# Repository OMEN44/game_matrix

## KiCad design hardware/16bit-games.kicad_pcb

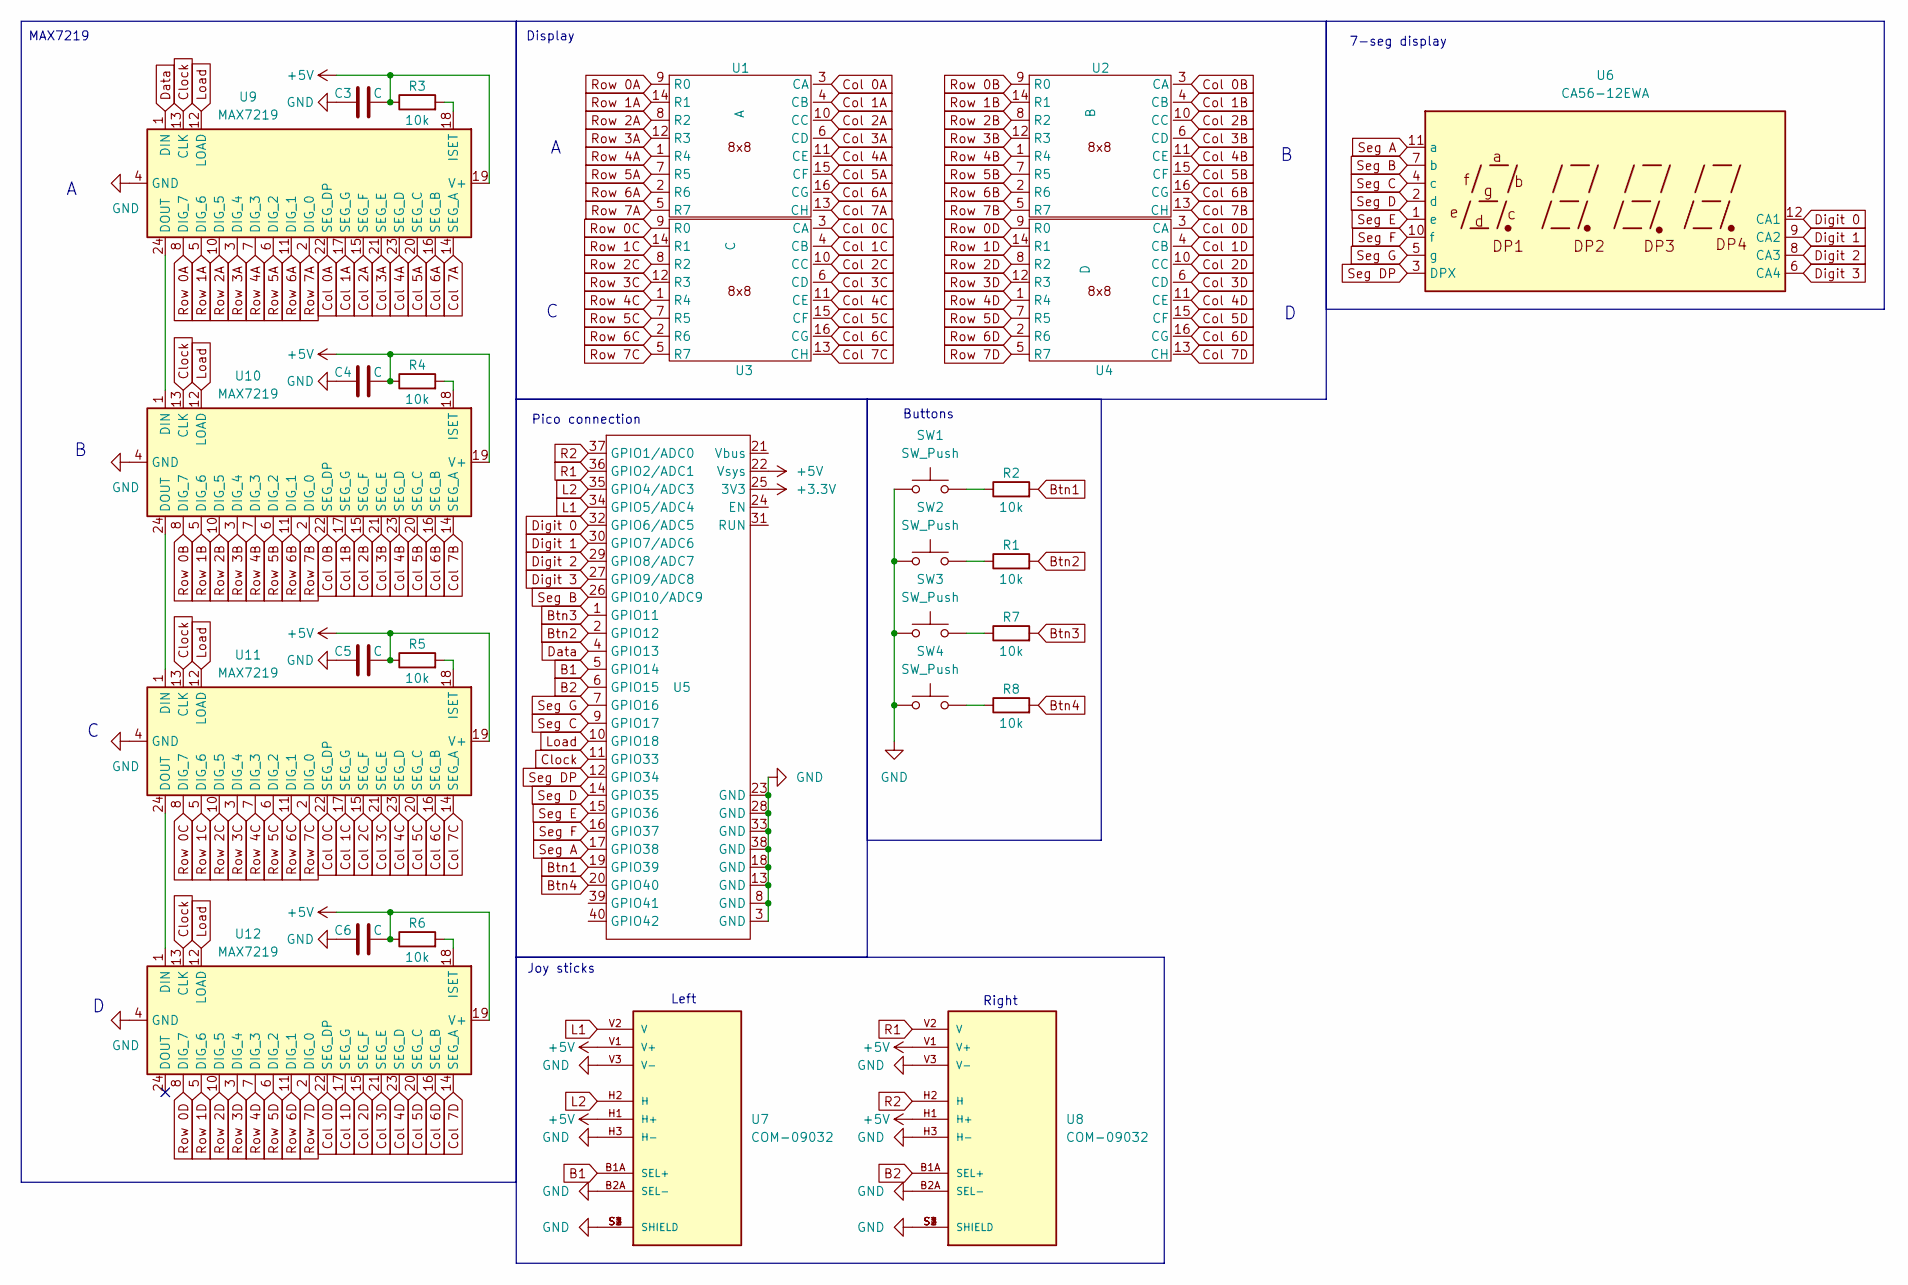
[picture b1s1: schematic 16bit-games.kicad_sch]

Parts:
C3, C4, C5, C6: C; C_Radial_D6.3mm_H5.0mm_P2.50mm
R1, R2, R3, R4, R5, R6, R7, R8: 10k; R_Axial_DIN0204_L3.6mm_D1.6mm_P7.62mm_Horizontal
SW1, SW2, SW3, SW4: SW_Push; SW_PUSH_6mm_H4.3mm
U1: A; 8x8
U2: B; 8x8
U3: C; 8x8
U4: D; 8x8
U5: ESP32-Pico
U6: CA56-12EWA; 4x7-seg Display
U7, U8: COM-09032; XDCR_COM-09032; PARTREV N/A
U9, U10, U11, U12: MAX7219; DIP-24_W7.62mm

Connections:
+3.3V: U5.25 (3V3)
+5V: C3.2, C4.2, C5.2, C6.2, R3.1, R4.1, R5.1, R6.1, U5.22 (Vsys), U7.H1 (H+), U7.V1 (V+), U8.H1 (H+), U8.V1 (V+), U9.19 (V+), U10.19 (V+), U11.19 (V+), U12.19 (V+)
B1: U5.5 (GPIO14), U7.B1A (SEL+)
B2: U5.6 (GPIO15), U8.B1A (SEL+)
Btn1: R2.2, U5.19 (GPIO39)
Btn2: R1.2, U5.2 (GPIO12)
Btn3: R7.2, U5.1 (GPIO11)
Btn4: R8.2, U5.20 (GPIO40)
Clock: U5.11 (GPIO33), U9.13 (CLK), U10.13 (CLK), U11.13 (CLK), U12.13 (CLK)
Col 0A: U1.3 (CA), U9.22 (SEG_DP)
Col 0B: U2.3 (CA), U10.22 (SEG_DP)
Col 0C: U3.3 (CA), U11.22 (SEG_DP)
Col 0D: U4.3 (CA), U12.22 (SEG_DP)
Col 1A: U1.4 (CB), U9.17 (SEG_G)
Col 1B: U2.4 (CB), U10.17 (SEG_G)
Col 1C: U3.4 (CB), U11.17 (SEG_G)
Col 1D: U4.4 (CB), U12.17 (SEG_G)
Col 2A: U1.10 (CC), U9.15 (SEG_F)
Col 2B: U2.10 (CC), U10.15 (SEG_F)
Col 2C: U3.10 (CC), U11.15 (SEG_F)
Col 2D: U4.10 (CC), U12.15 (SEG_F)
Col 3A: U1.6 (CD), U9.21 (SEG_E)
Col 3B: U2.6 (CD), U10.21 (SEG_E)
Col 3C: U3.6 (CD), U11.21 (SEG_E)
Col 3D: U4.6 (CD), U12.21 (SEG_E)
Col 4A: U1.11 (CE), U9.23 (SEG_D)
Col 4B: U2.11 (CE), U10.23 (SEG_D)
Col 4C: U3.11 (CE), U11.23 (SEG_D)
Col 4D: U4.11 (CE), U12.23 (SEG_D)
Col 5A: U1.15 (CF), U9.20 (SEG_C)
Col 5B: U2.15 (CF), U10.20 (SEG_C)
Col 5C: U3.15 (CF), U11.20 (SEG_C)
Col 5D: U4.15 (CF), U12.20 (SEG_C)
Col 6A: U1.16 (CG), U9.16 (SEG_B)
Col 6B: U2.16 (CG), U10.16 (SEG_B)
Col 6C: U3.16 (CG), U11.16 (SEG_B)
Col 6D: U4.16 (CG), U12.16 (SEG_B)
Col 7A: U1.13 (CH), U9.14 (SEG_A)
Col 7B: U2.13 (CH), U10.14 (SEG_A)
Col 7C: U3.13 (CH), U11.14 (SEG_A)
Col 7D: U4.13 (CH), U12.14 (SEG_A)
Data: U5.4 (GPIO13), U9.1 (DIN)
Digit 0: U5.32 (GPIO6/ADC5), U6.12 (CA1)
Digit 1: U5.30 (GPIO7/ADC6), U6.9 (CA2)
Digit 2: U5.29 (GPIO8/ADC7), U6.8 (CA3)
Digit 3: U5.27 (GPIO9/ADC8), U6.6 (CA4)
GND: C3.1, C4.1, C5.1, C6.1, SW1.1, SW2.1, SW3.1, SW4.1, U5.3 (GND), U5.8 (GND), U5.13 (GND), U5.18 (GND), U5.23 (GND), U5.28 (GND), U5.33 (GND), U5.38 (GND), U7.B2A (SEL-), U7.H3 (H-), U7.S1 (SHIELD), U7.S2 (SHIELD), U7.S3 (SHIELD), U7.S4 (SHIELD), U7.V3 (V-), U8.B2A (SEL-), U8.H3 (H-), U8.S1 (SHIELD), U8.S2 (SHIELD), U8.S3 (SHIELD), U8.S4 (SHIELD), U8.V3 (V-), U9.4 (GND), U9.9 (GND), U10.4 (GND), U10.9 (GND), U11.4 (GND), U11.9 (GND), U12.4 (GND), U12.9 (GND)
L1: U5.34 (GPIO5/ADC4), U7.V2 (V)
L2: U5.35 (GPIO4/ADC3), U7.H2 (H)
Load: U5.10 (GPIO18), U9.12 (LOAD), U10.12 (LOAD), U11.12 (LOAD), U12.12 (LOAD)
unnamed: R1.1, SW2.2
unnamed: R2.1, SW1.2
unnamed: R7.1, SW3.2
unnamed: R8.1, SW4.2
unnamed: R3.2, U9.18 (ISET)
unnamed: U9.24 (DOUT), U10.1 (DIN)
unnamed: U10.24 (DOUT), U11.1 (DIN)
unnamed: R4.2, U10.18 (ISET)
unnamed: U11.24 (DOUT), U12.1 (DIN)
unnamed: R5.2, U11.18 (ISET)
unnamed: R6.2, U12.18 (ISET)
R1: U5.36 (GPIO2/ADC1), U8.V2 (V)
R2: U5.37 (GPIO1/ADC0), U8.H2 (H)
Row 0A: U1.9 (R0), U9.8 (DIG_7)
Row 0B: U2.9 (R0), U10.8 (DIG_7)
Row 0C: U3.9 (R0), U11.8 (DIG_7)
Row 0D: U4.9 (R0), U12.8 (DIG_7)
Row 1A: U1.14 (R1), U9.5 (DIG_6)
Row 1B: U2.14 (R1), U10.5 (DIG_6)
Row 1C: U3.14 (R1), U11.5 (DIG_6)
Row 1D: U4.14 (R1), U12.5 (DIG_6)
Row 2A: U1.8 (R2), U9.10 (DIG_5)
Row 2B: U2.8 (R2), U10.10 (DIG_5)
Row 2C: U3.8 (R2), U11.10 (DIG_5)
Row 2D: U4.8 (R2), U12.10 (DIG_5)
Row 3A: U1.12 (R3), U9.3 (DIG_4)
Row 3B: U2.12 (R3), U10.3 (DIG_4)
Row 3C: U3.12 (R3), U11.3 (DIG_4)
Row 3D: U4.12 (R3), U12.3 (DIG_4)
Row 4A: U1.1 (R4), U9.7 (DIG_3)
Row 4B: U2.1 (R4), U10.7 (DIG_3)
Row 4C: U3.1 (R4), U11.7 (DIG_3)
Row 4D: U4.1 (R4), U12.7 (DIG_3)
Row 5A: U1.7 (R5), U9.6 (DIG_2)
Row 5B: U2.7 (R5), U10.6 (DIG_2)
Row 5C: U3.7 (R5), U11.6 (DIG_2)
Row 5D: U4.7 (R5), U12.6 (DIG_2)
Row 6A: U1.2 (R6), U9.11 (DIG_1)
Row 6B: U2.2 (R6), U10.11 (DIG_1)
Row 6C: U3.2 (R6), U11.11 (DIG_1)
Row 6D: U4.2 (R6), U12.11 (DIG_1)
Row 7A: U1.5 (R7), U9.2 (DIG_0)
Row 7B: U2.5 (R7), U10.2 (DIG_0)
Row 7C: U3.5 (R7), U11.2 (DIG_0)
Row 7D: U4.5 (R7), U12.2 (DIG_0)
Seg A: U5.17 (GPIO38), U6.11 (a)
Seg B: U5.26 (GPIO10/ADC9), U6.7 (b)
Seg C: U5.9 (GPIO17), U6.4 (c)
Seg D: U5.14 (GPIO35), U6.2 (d)
Seg DP: U5.12 (GPIO34), U6.3 (DPX)
Seg E: U5.15 (GPIO36), U6.1 (e)
Seg F: U5.16 (GPIO37), U6.10 (f)
Seg G: U5.7 (GPIO16), U6.5 (g)

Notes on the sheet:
Pico connection
Left
Display
MAX7219
Buttons
Right
Joy sticks
7-seg display

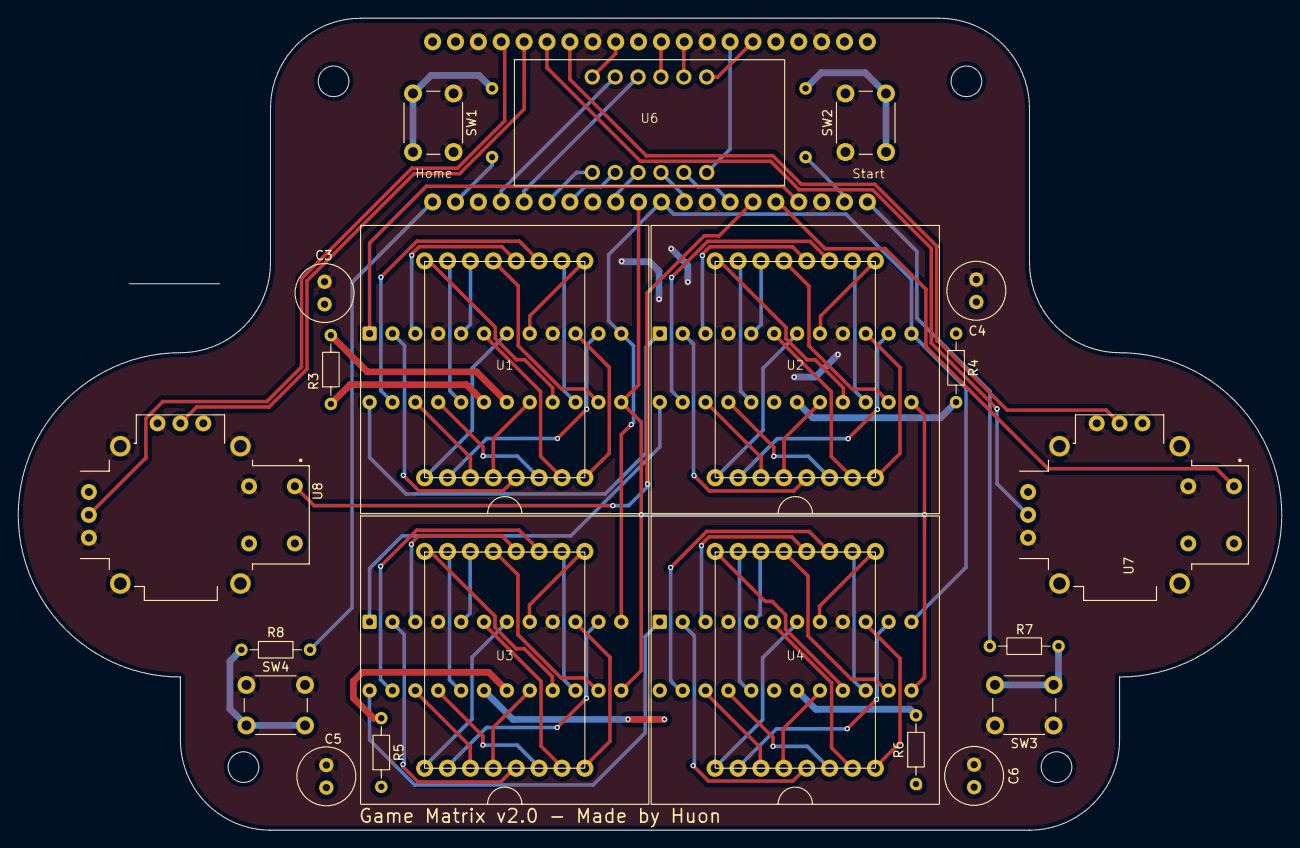
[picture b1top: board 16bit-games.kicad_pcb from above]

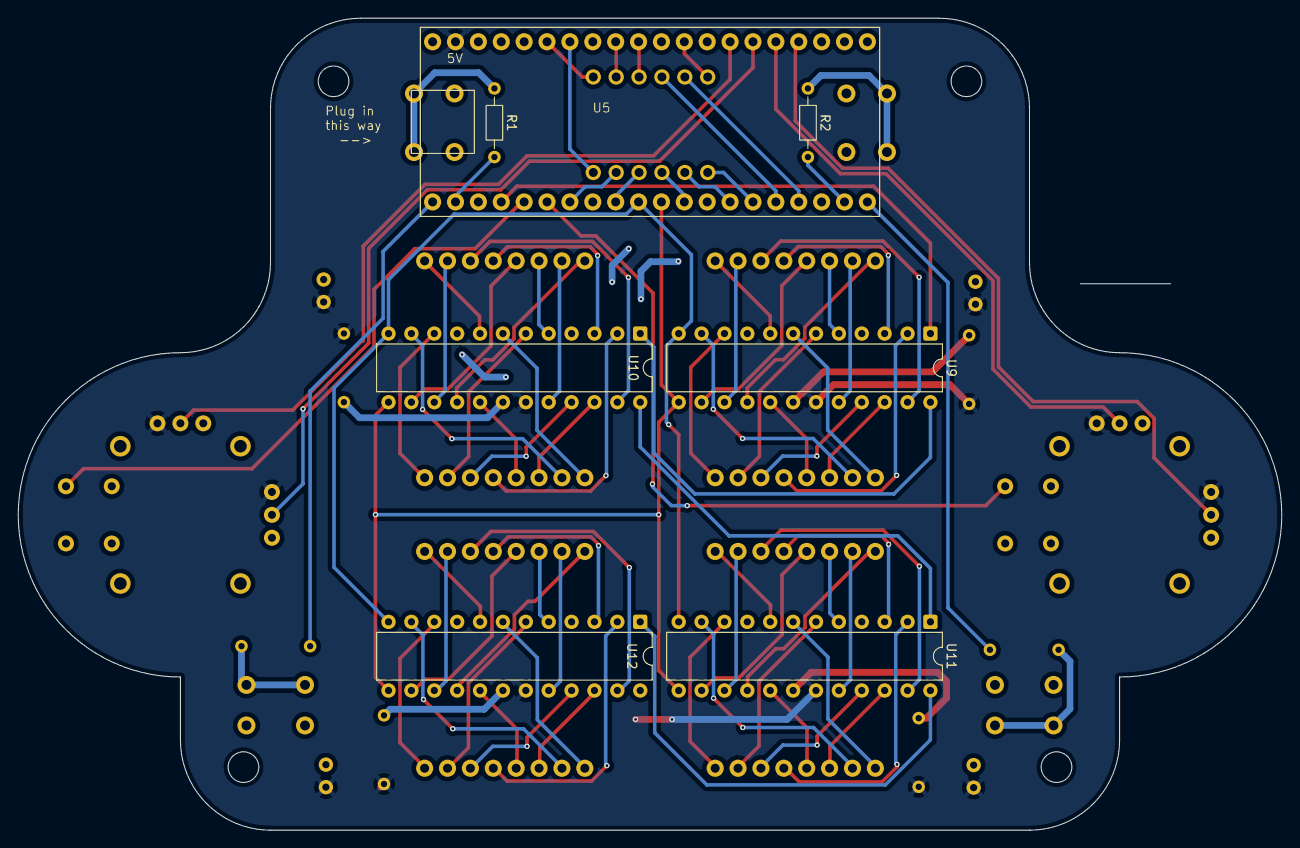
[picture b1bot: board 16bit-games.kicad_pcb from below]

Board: 2 copper layers, 140.2 x 90.1 mm, 28 parts (7 on the bottom side), 102 nets.
